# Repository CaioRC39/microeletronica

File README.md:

# Projeto de Microeletrônica
## *Projeto em grupo - Disciplina: Microeletrônica*
### Este projeto foi desenvolvido durante o 7º semestre (2025/2) da graduação em Engenharia da Computação, como trabalho prático da disciplina de Microeletrônica.

- Projeto completo de uma fonte linear estabilizada AC–DC, envolvendo dimensionamento elétrico (tensão, corrente e potência) de todos os componentes, incluindo ponte retificadora de 4 diodos, transistor de passagem e diodo Zener, com análise de custo e escolha baseada em custo-benefício.

- Simulação do circuito no LTSpice para validação dos valores calculados, seguida de montagem em protoboard, testes experimentais com osciloscópio e comparação entre valores teóricos, simulados e reais.

- Atuação como líder na organização e execução do projeto, incluindo soldagem em perfboard, testes finais do circuito e documentação técnica, simulando um fluxo completo de desenvolvimento de produto em ambiente industrial.

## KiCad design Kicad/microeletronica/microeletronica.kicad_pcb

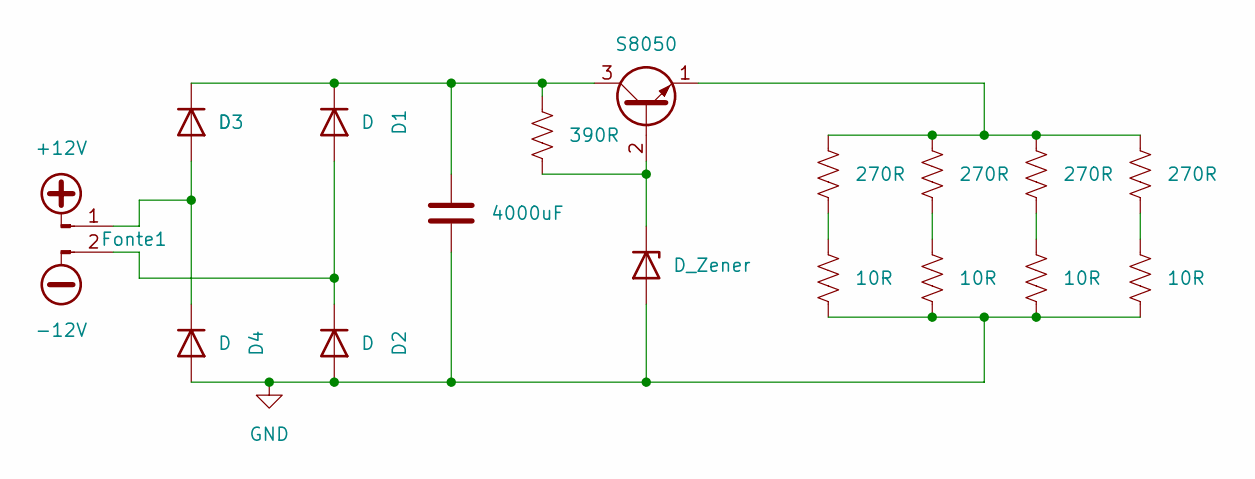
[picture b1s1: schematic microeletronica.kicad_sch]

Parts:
C1: 4000uF; CP_Radial_D5.0mm_P2.50mm
D1, D2, D3, D4: D; D_DO-41_SOD81_P10.16mm_Horizontal
D5: D_Zener; D_MiniMELF
Fonte1: Conn_01x02_Pin; PinHeader_1x02_P2.54mm_Vertical
Q1: S8050; TO-92_Inline
R1, R2, R5, R7: 270R; R_Axial_DIN0207_L6.3mm_D2.5mm_P10.16mm_Horizontal
R3, R4, R6, R8: 10R; R_Axial_DIN0207_L6.3mm_D2.5mm_P10.16mm_Horizontal
R9: 390R; R_Axial_DIN0207_L6.3mm_D2.5mm_P10.16mm_Horizontal

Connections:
GND: C1.2, D2.2 (A), D4.2 (A), D5.2 (A), R3.2, R4.2, R6.2, R8.2
unnamed: D1.2 (A), D2.1 (K), Fonte1.2
unnamed: C1.1, D1.1 (K), D3.1 (K), Q1.3 (C), R9.1
unnamed: D3.2 (A), D4.1 (K), Fonte1.1
unnamed: D5.1 (K), Q1.2 (B), R9.2
unnamed: Q1.1 (E), R1.1, R2.1, R5.1, R7.1
unnamed: R1.2, R3.1
unnamed: R2.2, R4.1
unnamed: R5.2, R6.1
unnamed: R7.2, R8.1

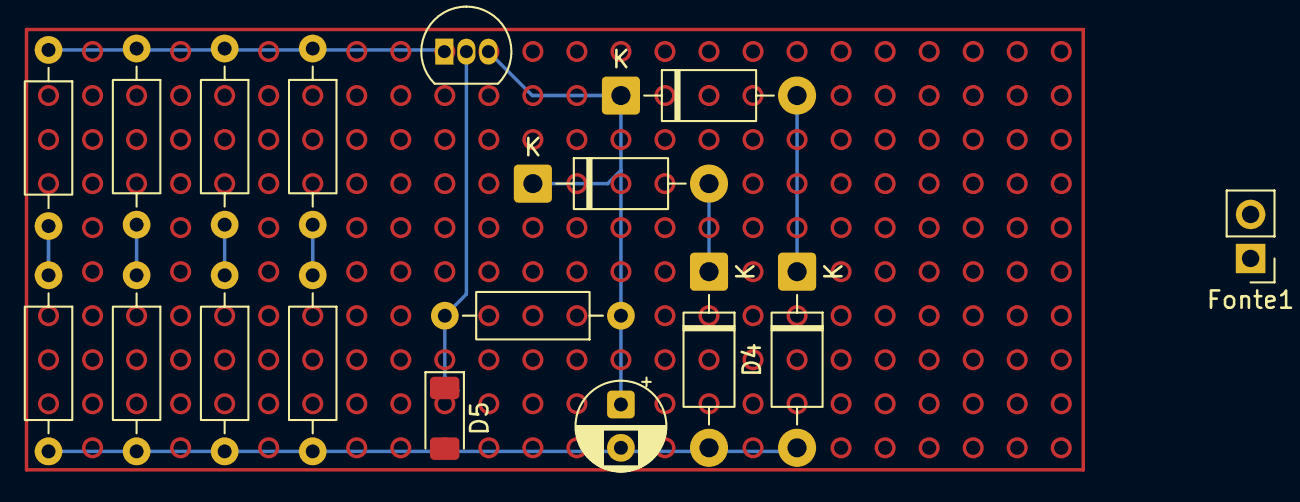
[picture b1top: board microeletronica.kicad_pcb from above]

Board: 2 copper layers, 17 parts (0 on the bottom side), 10 nets.

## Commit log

2026-01-09 Simulação Kicad
    Simulação de montagem dos componentes eletrônicos na perfboard utilizando o Kicad.
2026-01-09 Fotos
    Fotos do projeto montado e soldado na perfboard, além das leituras no osciloscópio.
2026-01-09 Simulação
    Simulação do projeto realizado no LTSpice
